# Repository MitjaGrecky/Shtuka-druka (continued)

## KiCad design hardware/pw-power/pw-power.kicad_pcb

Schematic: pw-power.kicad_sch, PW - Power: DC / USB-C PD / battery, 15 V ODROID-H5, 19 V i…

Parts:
C1: 10u; C_0805_2012Metric
C2: 4.7u; C_0603_1608Metric
C3: 10u 50V; C_1206_3216Metric
C4, C93, C105, C153: 10n 50V; C_0603_1608Metric
C5, C6: 47u 35V; CP_Elec_6.3x5.9; LCSC C178565
C7, C8: 330p; C_0402_1005Metric
C9, C10, C114, C115, C116, C121, C122, C123, C143, C144, C145, C150, C151, C152: 22u 25V; C_1210_3225Metric
C11, C125, C126, C129: 10u 25V; C_1210_3225Metric
C12: 47u 35V; CP_Elec_8x10.5
C13, C14, C15, C27, C36, C48, C110, C117, C139, C146: 100n 25V; C_0603_1608Metric
C16, C17, C37, C38: 47n 25V; C_0603_1608Metric
C18, C39: 4.7u 10V; C_0603_1608Metric
C19, C23, C40, C44, C57, C73, C74: 100n 50V; C_0603_1608Metric
C20, C21, C24, C25, C26, C41, C42, C45, C46, C47: 10u 35V; C_1206_3216Metric
C22, C43: 2.2u 35V; C_0805_2012Metric
C28, C29, C30, C31, C32, C33, C34, C49, C50, C51, C52, C53, C54, C55: 10u 25V; C_1206_3216Metric
C35, C56: 1n 50V; C_0402_1005Metric
C58, C61: 100n; C_0603_1608Metric
C59, C60, C111, C118, C124, C127, C140, C147: 1u; C_0603_1608Metric
C62: 100u 35V; CP_Elec_10x10.5
C63, C64: 150u 35V; CP_Elec_8x10.5; MPN EEH-ZA1V151P
C65, C66, C112, C119, C120, C141, C148: 10u 50V; C_1210_3225Metric
C67: 1u 50V; C_0805_2012Metric
C68: 220p; C_0402_1005Metric
C69, C86, C98: 100n; C_0402_1005Metric
C70: 33n; C_0402_1005Metric
C71: 560p; C_0402_1005Metric
C72, C131: 1u 25V; C_0603_1608Metric
C75: 47p; C_0402_1005Metric
C76, C77, C78, C79: 4.7u 50V; C_1210_3225Metric
C80, C81, C82, C83: 10u 35V; C_1210_3225Metric
C84, C85: 100u 35V; CP_Elec_8x10.5
C87, C99: 4.7u; C_0805_2012Metric
C88, C100: 47n; C_0603_1608Metric
C89, C90, C91, C92, C101, C102, C103, C104: 2.2u 50V; C_1206_3216Metric
C94, C95, C96, C97, C106, C107, C108, C109: 47u 10V; C_1210_3225Metric
C113, C142, C149: 220n 50V; C_0603_1608Metric
C128: 10n; C_0402_1005Metric
C130: 47u 25V; C_1210_3225Metric
C132: 47n; C_0402_1005Metric
C133: 22n; C_0402_1005Metric
C134: 470p; C_0402_1005Metric
C135, C136, C138: 4.7u 100V; C_1210_3225Metric
C137: 1u 100V; C_1206_3216Metric
C154, C155, C156, C157: 470u 25V; CP_Elec_10x10.5; MPN EEE-FK1E471P
D1, D2: SMBJ20CA; D_SMB; LCSC C151258
D3, D5: SMBJ13CA; D_SMB; LCSC C224008
D4, D6, D8: green; LED_0603_1608Metric; LCSC C84267
D7: SS1H10; D_SMA; LCSC C3151624
D9: BZT52C3V3; D_SOD-123; LCSC C173413
D10, D11: SS34; D_SMA; LCSC C8678
F1, F2: 10A; Fuse_2920_7451Metric
H1, H2, H3, H4: M3; MountingHole_3.2mm_M3_ISO7380
J1: USB-C Power in; Molex_Micro-Fit_3.0_43045-0612_2x03_P3.00mm_Vertical; LCSC C234188
J2: Battery 1; Molex_Micro-Fit_3.0_43045-0612_2x03_P3.00mm_Vertical; LCSC C234188
J3: Battery 2; Molex_Micro-Fit_3.0_43045-0612_2x03_P3.00mm_Vertical; LCSC C234188
J4: On/Off switch; Molex_Micro-Fit_3.0_43045-0412_2x02_P3.00mm_Vertical; LCSC C277721
J5: Power telemetry to P2; JST_PH_B8B-PH-K_1x08_P2.00mm_Vertical; LCSC C157974
J6: 15 V to H5; Molex_Micro-Fit_3.0_43045-0412_2x02_P3.00mm_Vertical; LCSC C277721
J7: +5V panel; Molex_Micro-Fit_3.0_43045-0612_2x03_P3.00mm_Vertical; LCSC C234188
J8: to R2; JST_PH_B5B-PH-K_1x05_P2.00mm_Vertical; LCSC C157993
J9: to A1/R1; Molex_Micro-Fit_3.0_43045-1012_2x05_P3.00mm_Vertical; LCSC C277725
J10: to F1; JST_PH_B4B-PH-K_1x04_P2.00mm_Vertical; LCSC C131334
J11: +5V screen; JST_PH_B2B-PH-K_1x02_P2.00mm_Vertical; LCSC C131337
J12: Fan 12 V PWM; PinHeader_1x04_P2.54mm_Vertical; LCSC C2691448
L1, L2: 1uH; L_Bourns_SRP7028A_7.3x6.6mm; LCSC C87572
L3: 4.7uH; L_Bourns_SRP1245A
L4, L5: 4.7uH; L_Bourns_SRP1038C_10.0x10.0mm; MPN SRP1038CC-4R7M
L6, L7, L9, L10: 10uH; L_Bourns_SRN6045TA
L8: 22uH; L_Bourns_SRN6045TA
Q1, Q2, Q3, Q6, Q9, Q10, Q11, Q12: CSD18532Q5B; TDSON-8-1; LCSC C882766
Q4, Q5, Q7, Q8: 2N7002; SOT-23; LCSC C8545
Q13: IRLML0100; SOT-23; LCSC C53658
R1, R3: 42.2k; R_0402_1005Metric
R2, R4, R5, R6, R7, R8, R18, R19, R29, R30, R34, R35, R42, R45, R71, R73, R77, R84: 10k; R_0402_1005Metric
R9, R20: 0 wire 1mm2; SolderWire-1sqmm_1x02_P5.4mm_D1.4mm_OD2.7mm
R10, R21: 2; R_0805_2012Metric
R11, R22, R75, R83, R85: 100; R_0402_1005Metric
R12, R23: 10.5k; R_0402_1005Metric
R13, R24: 47k; R_0402_1005Metric
R14, R16, R25, R27, R36, R53, R60, R62, R64, R68, R79, R81: 100k; R_0402_1005Metric
R15, R26: 9.31k; R_0402_1005Metric
R17, R28, R78: 2.2k; R_0402_1005Metric
R31: 5m; R_2512_6332Metric
R32, R33, R37: 10; R_0603_1608Metric
R38: 249k; R_0402_1005Metric
R39: 32.4k; R_0402_1005Metric
R40: 93.1k; R_0402_1005Metric
R41: 27.4k; R_0402_1005Metric
R43: 453k; R_0402_1005Metric
R44: 20k; R_0402_1005Metric
R46: 8m; R_2512_6332Metric
R47: 100; R_0603_1608Metric
R48, R55: 392k; R_0402_1005Metric
R49, R56, R70: 49.9k; R_0402_1005Metric
R50, R57: 54.9k; R_0402_1005Metric
R51, R58: 41.2k; R_0402_1005Metric
R52, R59: 24.9k; R_0402_1005Metric
R54, R61: 6.8m; R_2512_6332Metric
R63, R65: 7.68k; R_0402_1005Metric
R66: 102k; R_0402_1005Metric
R67: 11k; R_0402_1005Metric
R69: 27k; R_0402_1005Metric
R72: 475k; R_0402_1005Metric
R74: 0.1; R_0603_1608Metric
R76: 383k; R_0402_1005Metric
R80: 7.15k; R_0402_1005Metric
R82: 9.09k; R_0402_1005Metric
R86: 357k; R_0402_1005Metric
R87: 118k; R_0402_1005Metric
R88: 26.7k; R_0402_1005Metric
R89: 3.32k; R_0402_1005Metric
R90: 220k; R_0402_1005Metric
R91, R93: 0; R_1206_3216Metric
R92, R94: 10; R_2512_6332Metric
R95, R96, R97, R98, R99, R100: 1k; R_2512_6332Metric
R101, R102: 820; R_2512_6332Metric
TP1: VBUS; TestPoint_Pad_D2.0mm
TP2: BUS; TestPoint_Pad_D2.0mm
TP3: P14; TestPoint_Pad_D2.0mm
TP4: N14; TestPoint_Pad_D2.0mm
TP5: +5V; TestPoint_Pad_D2.0mm
TP6: +5V_PANEL; TestPoint_Pad_D2.0mm
TP7: +3V3; TestPoint_Pad_D2.0mm
TP8, TP9, TP10: GND; TestPoint_Pad_D2.0mm
U1: TPS25730D; Texas_REF0038A_WQFN-38-2EP_6x4mm_P0.4; LCSC C22438973
U2, U3, U4, U6: LM74700-Q1; SOT-23-6; LCSC C2941042
U5, U7: BQ25798; Texas_RQM0029A_VQFN-29_4x4mm_P0.4mm; LCSC C2876593
U8: INA226; MSOP-10_3x3mm_P0.5mm; LCSC C49851
U9: AP2112K-3.3; SOT-23-5; LCSC C51118
U10: TCA9546APW; TSSOP-16_4.4x5mm_P0.65mm; LCSC C201653
U11: LM5176; HTSSOP-28-1EP_4.4x9.7mm_P0.65mm_EP3.4x9.5mm_ThermalVias; LCSC C442493
U12, U13: LM70660; VQFN-29_RRX0029B_6x6_P0.5mm; LCSC C42328952
U14, U15, U20, U21: LMR33640; Texas_HSOP-8-1EP_3.9x4.9mm_P1.27mm_ThermalVias; LCSC C2836966
U16: TPS7A4701; Texas_RGW0020A_VQFN-20-1EP_5x5mm_P0.65mm_EP3.15x3.15mm_Ther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; LCSC C90084
U17: TPS7A3301; Texas_RGW0020A_VQFN-20-1EP_5x5mm_P0.65mm_EP3.15x3.15mm_Ther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; LCSC C90082
U18: LM5156H; Texas_HTSSOP-14-1EP_4.4x5mm_P0.65mm_EP3.4x5mm_Mask3.155x3.2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; LCSC C2867852
U19: TPS7A4101; Texas_DGN0008B_VSSOP-8-1EP_3x3mm_P0.65mm_EP2x3mm_Mask1.88x1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; LCSC C111739
U22: TPS26631RGER; QFN-24-1EP_4x4mm_P0.5mm_EP2.65x2.65mm; LCSC C1850273

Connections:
+3V3: C58.1, C60.1, C61.1, Q5.1 (G), Q8.1 (G), R18.2, R19.2, R29.2, R30.2, R34.2, R35.2, R84.2, TP7.1, U8.6 (VS), U9.5 (VOUT), U10.16 (VCC)
+5V: C59.1, C106.1, C107.1, C108.1, C109.1, J8.5, J9.5, J9.9, J10.4, J11.1, R61.2, R78.1, TP5.1, U9.1 (VIN), U9.3 (EN), U13.6 (BIAS), U13.12 (VOUT)
/+5V_PANEL: C94.1, C95.1, C96.1, C97.1, J7.1, J7.2, J7.3, R54.2, TP6.1, U12.6 (BIAS), U12.12 (VOUT)
/+12V: C126.1, J8.1, J9.1, J10.1, U16.1 (OUT), U16.3 (SENSE/FB), U16.20 (OUT)
/+48V: C138.1, J9.7, R76.1, U19.1 (OUT)
/-12V: C128.1, C130.2, J8.3, J9.3, J10.3, R66.1, U17.1 (OUT), U17.20 (OUT)
/B19_BOOT1: C73.1, U11.26 (BOOT1)
/B19_BOOT2: C74.1, U11.20 (BOOT2)
/B19_CMP_RC: C70.1, R42.2
/B19_COMP: C71.1, R42.1, U11.9 (COMP)
/B19_CS: C75.1, R47.2, U11.16 (CS)
/B19_CSN: Q10.1 (S), Q10.2 (S), Q10.3 (S), Q12.1 (S), Q12.2 (S), Q12.3 (S), R46.1, R47.1
/B19_FB: R43.2, R44.1, U11.11 (FB)
/B19_HDRV1: Q9.4 (G), U11.27 (HDRV1)
/B19_HDRV2: Q11.4 (G), U11.19 (HDRV2)
/B19_LDRV1: Q10.4 (G), U11.25 (LDRV1)
/B19_LDRV2: Q12.4 (G), U11.21 (LDRV2)
/B19_MODE: R40.1, U11.4 (MODE)
/B19_PG: R45.1, U11.17 (PGOOD)
/B19_RT: R41.1, U11.6 (RT/SYNC)
/B19_SLOPE: C68.1, U11.7 (SLOPE)
/B19_SS: C69.1, U11.8 (SS)
/B19_SW1: C73.2, L3.1, Q9.1 (S), Q9.2 (S), Q9.3 (S), Q10.5 (D), U11.28 (SW1)
/B19_SW2: C74.2, L3.2, Q11.1 (S), Q11.2 (S), Q11.3 (S), Q12.5 (D), U11.18 (SW2)
/B19_UVLO: R38.2, R39.1, U11.1 (EN/UVLO)
/B19_VCC: C72.1, R45.2, U11.23 (VCC)
/B19_VIN: C67.1, R37.2, U11.2 (VIN), U11.3 (VISNS)
/BAT1_F: C15.2, C33.1, C34.1, D3.1 (A1), F1.2, Q3.1 (S), Q3.2 (S), Q3.3 (S), R11.1, U4.3 (EN), U4.6 (ANODE), U5.22 (BAT), U5.23 (BAT)
/BAT1_J: F1.1, R9.2
/BAT1_RAW: J2.1, J2.2, R9.1
/BAT2_F: C36.2, C54.1, C55.1, D5.1 (A1), F2.2, Q6.1 (S), Q6.2 (S), Q6.3 (S), R22.1, U6.3 (EN), U6.6 (ANODE), U7.22 (BAT), U7.23 (BAT)
/BAT2_J: F2.1, R20.2
/BAT2_RAW: J3.1, J3.2, R20.1
/BUS: C62.1, C63.1, C64.1, C65.1, C66.1, C76.1, C77.1, C78.1, C79.1, C89.1, C90.1, C91.1, C92.1, C93.1, C101.1, C102.1, C103.1, C104.1, C105.1, Q9.5 (D), R31.2, R33.1, R37.1, R38.1, R48.1, R55.1, TP2.1, U8.8 (Vbus), U12.1 (VIN), U12.2 (VIN), U12.3 (VIN), U12.27 (VIN), U12.28 (VIN), U12.29 (VIN), U13.1 (VIN), U13.2 (VIN), U13.3 (VIN), U13.27 (VIN), U13.28 (VIN), U13.29 (VIN)
/BUS_IN: J4.1, J4.2, Q2.5 (D), Q3.5 (D), Q6.5 (D), U3.4 (CATHODE), U4.4 (CATHODE), U6.4 (CATHODE)
/BUS_SW: J4.3, J4.4, R31.1, R32.1
/CH1_BATP: R11.2, U5.18 (BATP)
/CH1_BTST1: C16.1, U5.4 (BTST1)
/CH1_BTST2: C17.1, U5.19 (BTST2)
/CH1_CE: Q4.3 (D), R16.2, U5.13 (~CE)
/CH1_CEM: Q4.2 (S), Q5.3 (D)
/CH1_ILIM: R13.2, R14.1, U5.17 (ILIM_HIZ)
/CH1_LEDA: D4.2 (A), R17.2
/CH1_PMID: C23.1, C24.1, C25.1, C26.1, U5.29 (PMID)
/CH1_PROG: R12.1, U5.20 (PROG)
/CH1_REGN: C18.1, R13.1, R15.1, R16.1, R17.1, U5.5 (REGN)
/CH1_SCL: R18.1, U5.14 (SCL), U10.5 (SC0)
/CH1_SDA: R19.1, U5.15 (SDA), U10.4 (SD0)
/CH1_SDRV: C35.1, U5.24 (SDRV)
/CH1_SNUB: C22.1, R10.2
/CH1_STAT: D4.1 (K), U5.1 (STAT)
/CH1_SW1: C16.2, L1.1, U5.28 (SW1)
/CH1_SW2: C17.2, L1.2, U5.26 (SW2)
/CH1_SYS: C27.1, C28.1, C29.1, C30.1, C31.1, C32.1, U5.25 (SYS)
/CH1_TS: J2.5, R15.2, U5.16 (TS)
/CH2_BATP: R22.2, U7.18 (BATP)
/CH2_BTST1: C37.1, U7.4 (BTST1)
/CH2_BTST2: C38.1, U7.19 (BTST2)
/CH2_CE: Q7.3 (D), R27.2, U7.13 (~CE)
/CH2_CEM: Q7.2 (S), Q8.3 (D)
/CH2_ILIM: R24.2, R25.1, U7.17 (ILIM_HIZ)
/CH2_LEDA: D6.2 (A), R28.2
/CH2_PMID: C44.1, C45.1, C46.1, C47.1, U7.29 (PMID)
/CH2_PROG: R23.1, U7.20 (PROG)
/CH2_REGN: C39.1, R24.1, R26.1, R27.1, R28.1, U7.5 (REGN)
/CH2_SCL: R29.1, U7.14 (SCL), U10.7 (SC1)
/CH2_SDA: R30.1, U7.15 (SDA), U10.6 (SD1)
/CH2_SDRV: C56.1, U7.24 (SDRV)
/CH2_SNUB: C43.1, R21.2
/CH2_STAT: D6.1 (K), U7.1 (STAT)
/CH2_SW1: C37.2, L2.1, U7.28 (SW1)
/CH2_SW2: C38.2, L2.2, U7.26 (SW2)
/CH2_SYS: C48.1, C49.1, C50.1, C51.1, C52.1, C53.1, U7.25 (SYS)
/CH2_TS: J3.5, R26.2, U7.16 (TS)
/CHG_EN: J5.8, Q4.1 (G), Q7.1 (G), R36.1
/CHG_INT: J5.4, R35.1, U5.21 (~INT), U7.21 (~INT)
/EXT: C14.2, C19.1, C20.1, C21.1, C40.1, C41.1, C42.1, D2.1 (A1), Q1.5 (D), Q2.1 (S), Q2.2 (S), Q2.3 (S), R10.1, R21.1, U2.4 (CATHODE), U3.3 (EN), U3.6 (ANODE), U5.2 (VBUS), U5.3 (VBUS), U5.8 (VAC2), U5.9 (VAC1), U7.2 (VBUS), U7.3 (VBUS), U7.8 (VAC2), U7.9 (VAC1)
/FAN_PWM: J12.4, R83.2
/FAN_PWM_IN: J5.5, R83.1
/FAN_TACH: J12.3, R84.1, R85.1
/FAN_TACH_OUT: J5.6, R85.2
/HV_COMP: C134.1, R71.1, U18.8 (COMP)
/HV_CRC: C133.1, R71.2
/HV_CS: R75.2, U18.7 (CS)
/HV_CSN: Q13.2 (S), R74.1, R75.1
/HV_FB: R72.2, R73.1, U18.10 (FB)
/HV_GATE: Q13.1 (G), U18.4 (GATE)
/HV_RAW: C135.1, C136.1, C137.1, D7.1 (K), R72.1, U19.5 (EN), U19.8 (IN)
/HV_RT: R70.1, U18.12 (RT)
/HV_SS: C132.1, U18.11 (SS)
/HV_SW: D7.2 (A), L8.2, Q13.3 (D)
/HV_UVLO: R68.2, R69.1, U18.14 (EN/UVLO/SYNC)
/HV_VCC: C131.1, U18.3 (VCC), U18.9 (DITHOFF)
/IBAT1_GATE: Q3.4 (G), U4.5 (GATE)
/IBAT1_VCAP: C15.1, U4.1 (VCAP)
/IBAT2_GATE: Q6.4 (G), U6.5 (GATE)
/IBAT2_VCAP: C36.1, U6.1 (VCAP)
/IEXT_GATE: Q2.4 (G), U3.5 (GATE)
/IEXT_VCAP: C14.1, U3.1 (VCAP)
/IPD_GATE: Q1.4 (G), U2.5 (GATE)
/IPD_VCAP: C13.1, U2.1 (VCAP)
/LED_K: D8.2 (A), R78.2
/MUX_RST: R34.1, U10.3 (~RESET)
/N12_FB: C128.2, R66.2, R67.1, U17.3 (FB)
/N12_NR: C127.1, U17.14 (NR/SS)
/N14: C118.2, C119.2, C121.2, C122.2, C123.2, C129.2, D11.2 (A), R65.2, R94.1, R97.1, R98.1, TP4.1, U15.1 (GND), U15.9 (GND), U17.13 (EN), U17.15 (IN), U17.16 (IN)
/N14_BOOT: C117.1, U15.7 (BOOT)
/N14_C: C156.2, C157.2, R93.2
/N14_FB: R64.2, R65.1, U15.5 (FB)
/N14_ST: D11.1 (K), R93.1, R94.2
/N14_SW: C117.2, L7.1, U15.8 (SW)
/N14_VCC: C118.1, U15.6 (VCC)
/P5VPANEL_BOOT: C88.1, U12.4 (CBOOT)
/P5VPANEL_CFG: R51.1, U12.13 (CONFIG)
/P5VPANEL_EN: R48.2, R49.1, U12.9 (EN/UVLO)
/P5VPANEL_FB: R52.1, U12.16 (FB)
/P5VPANEL_LS: L4.2, R54.1, U12.11 (ISNS+)
/P5VPANEL_RT: R50.1, U12.14 (RT)
/P5VPANEL_SW: C88.2, L4.1, U12.5 (SW4), U12.20 (SW), U12.21 (SW), U12.22 (SW)
/P5VPANEL_VCC: C87.1, U12.19 (VCC)
/P5VPANEL_VDDA: C86.1, R52.2, R53.2, U12.18 (VDDA)
/P5VPANEL_XC: R53.1, U12.15 (EXTCOMP)
/P5V_BOOT: C100.1, U13.4 (CBOOT)
/P5V_CFG: R58.1, U13.13 (CONFIG)
/P5V_EN: R55.2, R56.1, U13.9 (EN/UVLO)
/P5V_FB: R59.1, U13.16 (FB)
/P5V_LS: L5.2, R61.1, U13.11 (ISNS+)
/P5V_RT: R57.1, U13.14 (RT)
/P5V_SW: C100.2, L5.1, U13.5 (SW4), U13.20 (SW), U13.21 (SW), U13.22 (SW)
/P5V_VCC: C99.1, U13.19 (VCC)
/P5V_VDDA: C98.1, R59.2, R60.2, U13.18 (VDDA)
/P5V_XC: R60.1, U13.15 (EXTCOMP)
/P12_NR: C124.1, U16.14 (NR)
/P14: C114.1, C115.1, C116.1, C125.1, D10.1 (K), L6.2, R62.1, R92.1, R95.1, R96.1, TP3.1, U16.13 (EN), U16.15 (IN), U16.16 (IN)
/P14_BOOT: C110.1, U14.7 (BOOT)
/P14_C: C154.1, C155.1, R91.2
/P14_FB: R62.2, R63.1, U14.5 (FB)
/P14_ST: D10.2 (A), R91.1, R92.2
/P14_SW: C110.2, L6.1, U14.8 (SW)
/P14_VCC: C111.1, U14.6 (VCC)
/P48_FB: R76.2, R77.1, U19.2 (FB)
/PDF_DVDT: C153.1, U22.9 (dVdT)
/PDF_ILIM: R89.1, U22.10 (ILIM)
/PDF_OV: R87.2, R88.1, U22.7 (OVP)
/PDF_SHDN: D9.2 (K), R90.2, U22.12 (SHDN)
/PDF_UV: R86.2, R87.1, U22.6 (UVLO)
/PD_ADCIN1: R1.2, R2.1, U1.2 (ADCIN1)
/PD_ADCIN34: R3.2, R4.1, U1.5 (ADCIN3), U1.7 (ADCIN4)
/PD_CC1: C7.1, J1.5, U1.28 (CC1)
/PD_CC2: C8.1, J1.6, U1.29 (CC2)
/PD_DRAIN: U1.15 (DRAIN), U1.30 (DRAIN), U1.40 (DRAIN)
/PD_FAULT: R5.1, U1.18 (~FAULT_IN)
/PD_LDO1V5: C2.1, U1.4 (LDO_1V5)
/PD_LDO3V3: C1.1, R1.1, R3.1, R5.2, U1.1 (LDO_3V3), U1.3 (ADCIN2)
/PD_OUT: C9.1, C10.1, C11.1, C12.1, C13.2, Q1.1 (S), Q1.2 (S), Q1.3 (S), U1.20 (PPHV), U2.3 (EN), U2.6 (ANODE)
/PD_RSV26: R6.1, U1.26 (RESERVED)
/PD_RSV27: R7.1, U1.27 (RESERVED)
/PD_RSV36: R8.1, U1.36 (RESERVED)
/PD_VBUS: C5.1, C6.1, D1.1 (A1), J1.1, J1.2, R86.1, R90.1, TP1.1, U22.1 (IN), U22.2 (IN), U22.5 (IN_SYS)
/PD_VBUSF: C3.1, C4.1, U1.23 (VBUS_IN), U1.32 (VBUS), U22.17 (OUT), U22.18 (OUT)
/PM_ALERT: J5.3, U8.3 (~Alert)
/PM_INN: C57.2, R33.2, U8.9 (Vin-)
/PM_INP: C57.1, R32.2, U8.10 (Vin+)
/PM_SCL: J5.2, U8.5 (SCL), U10.14 (SCL)
/PM_SDA: J5.1, U8.4 (SDA), U10.15 (SDA)
/V12F: C150.1, C151.1, C152.1, J12.2, L10.2, R81.1, R101.1, R102.1
/V12F_BOOT: C146.1, U21.7 (BOOT)
/V12F_FB: R81.2, R82.1, U21.5 (FB)
/V12F_SW: C146.2, L10.1, U21.8 (SW)
/V12F_VCC: C147.1, U21.6 (VCC)
/V15: C143.1, C144.1, C145.1, J6.1, J6.2, L9.2, R79.1, R99.1, R100.1
/V15_BOOT: C139.1, U20.7 (BOOT)
/V15_FB: R79.2, R80.1, U20.5 (FB)
/V15_SW: C139.2, L9.1, U20.8 (SW)
/V15_VCC: C140.1, U20.6 (VCC)
/V19: C80.1, C81.1, C82.1, C83.1, C84.1, C85.1, C112.1, C113.1, C119.1, C120.1, C141.1, C142.1, C148.1, C149.1, L8.1, Q11.5 (D), R43.1, R68.1, U11.12 (VOSNS), U11.13 (ISNS(-)), U11.14 (ISNS(+)), U11.24 (BIAS), U14.2 (VIN), U14.3 (EN), U15.2 (VIN), U15.3 (EN), U18.1 (BIAS), U20.2 (VIN), U20.3 (EN), U21.2 (VIN), U21.3 (EN)
GND: C1.2, C2.2, C3.2, C4.2, C5.2, C6.2, C7.2, C8.2, C9.2, C10.2, C11.2, C12.2, C18.2, C19.2, C20.2, C21.2, C22.2, C23.2, C24.2, C25.2, C26.2, C27.2, C28.2, C29.2, C30.2, C31.2, C32.2, C33.2, C34.2, C35.2, C39.2, C40.2, C41.2, C42.2, C43.2, C44.2, C45.2, C46.2, C47.2, C48.2, C49.2, C50.2, C51.2, C52.2, C53.2, C54.2, C55.2, C56.2, C58.2, C59.2, C60.2, C61.2, C62.2, C63.2, C64.2, C65.2, C66.2, C67.2, C68.2, C69.2, C70.2, C71.2, C72.2, C75.2, C76.2, C77.2, C78.2, C79.2, C80.2, C81.2, C82.2, C83.2, C84.2, C85.2, C86.2, C87.2, C89.2, C90.2, C91.2, C92.2, C93.2, C94.2, C95.2, C96.2, C97.2, C98.2, C99.2, C101.2, C102.2, C103.2, C104.2, C105.2, C106.2, C107.2, C108.2, C109.2, C111.2, C112.2, C113.2, C114.2, C115.2, C116.2, C120.2, C121.1, C122.1, C123.1, C124.2, C125.2, C126.2, C127.2, C129.1, C130.1, C131.2, C132.2, C133.2, C134.2, C135.2, C136.2, C137.2, C138.2, C140.2, C141.2, C142.2, C143.2, C144.2, C145.2, C147.2, C148.2, C149.2, C150.2, C151.2, C152.2, C153.2, C154.2, C155.2, C156.1, C157.1, D1.2 (A2), D2.2 (A2), D3.2 (A2), D5.2 (A2), D8.1 (K), D9.1 (A), J1.3, J1.4, J2.3, J2.4, J2.6, J3.3, J3.4, J3.6, J5.7, J6.3, J6.4, J7.4, J7.5, J7.6, J8.2, J8.4, J9.2, J9.4, J9.6, J9.8, J9.10, J10.2, J11.2, J12.1, L7.2, Q5.2 (S), Q8.2 (S), R2.2, R4.2, R6.2, R7.2, R8.2, R12.2, R14.2, R23.2, R25.2, R36.2, R39.2, R40.2, R41.2, R44.2, R46.2, R49.2, R50.2, R51.2, R56.2, R57.2, R58.2, R63.2, R64.1, R67.2, R69.2, R70.2, R73.2, R74.2, R77.2, R80.2, R82.2, R88.2, R89.2, R95.2, R96.2, R97.2, R98.2, R99.2, R100.2, R101.2, R102.2, TP8.1, TP9.1, TP10.1, U1.8 (I2Ct_SDA), U1.9 (I2Ct_SCL), U1.11 (GND), U1.12 (GND), U1.14 (GND), U1.16 (GND), U1.17 (GND), U1.31 (GND), U1.34 (GND), U1.38 (VIN_3V3), U1.39 (GND), U2.2 (GND), U3.2 (GND), U4.2 (GND), U5.10 (ACDRV2), U5.11 (ACDRV1), U5.27 (GND), U6.2 (GND), U7.10 (ACDRV2), U7.11 (ACDRV1), U7.27 (GND), U8.1 (A1), U8.2 (A0), U8.7 (GND), U9.2 (GND), U10.1 (A0), U10.2 (A1), U10.8 (GND), U10.13 (A2), U11.5 (DITH), U11.10 (AGND), U11.15 (CSG), U11.22 (PGND), U11.29 (PowerPAD), U12.8 (PFM/SYNCIN), U12.17 (AGND), U12.23 (PGND), U12.24 (PGND), U12.25 (PGND), U12.26 (PGND), U12.30 (EP), U13.8 (PFM/SYNCIN), U13.17 (AGND), U13.23 (PGND), U13.24 (PGND), U13.25 (PGND), U13.26 (PGND), U13.30 (EP), U14.1 (GND), U14.9 (GND), U16.4 (6.4V), U16.6 (3.2V), U16.7 (GND), U16.9 (0.8V), U16.11 (0.2V), U16.21 (EP), U17.7 (GND), U17.21 (EP), U18.5 (PGND), U18.6 (AGND), U18.15 (AGND), U19.4 (GND), U19.9 (GND), U20.1 (GND), U20.9 (GND), U21.1 (GND), U21.9 (GND), U22.8 (GND), U22.11 (MODE), U22.15 (PGTH), U22.25 (EP)

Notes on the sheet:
Input USB-C PD 15-20 V (TPS25730D, also a MacBook charger; the DC input is removed, R205) -> EXT; EXT and two 3S packs (each with its own BQ25798 charger from EXT) -> ideal diodes (LM74700) -> rear On/Off switch -> BUS 9-24 V (packs 9-12.6 V) -> 19 V internal rail (LM5176) -> 15 V H5 (LMR33640), +5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
Values after the TI datasheet examples, scaled; every 'check' note is verified before the board
Rev 0.1: schematic only (R145: USB-C Power is separate from the isolated USB-C PC port)

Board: 4 copper layers, 343 parts (243 on the bottom side), 177 nets, no tracks yet.

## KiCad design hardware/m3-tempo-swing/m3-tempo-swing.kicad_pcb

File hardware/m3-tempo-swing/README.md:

# M3 - Tempo + Swing (encoder module)

Two smooth encoders with push (Tempo, Swing) and a 12-LED RGB ring around each. Spec: `hardware/for-routing/SPEC_boards.md`, section M3.
Status: rev 0.2 (rings r 15 from the layout, V2) - schematic and placed board with mounts, not routed (`UNROUTED`). Package for EasyEDA Pro: `hardware/for-routing/M3/`.

| | |
|---|---|
| Board | 92 x 34 mm, 2 layers; panel x 10-102, y 263-297 (the M1 strip, left column) |
| Top side | 2 x Alps EC11E smooth with switch (shafts at panel x 32 and 80, y 277; knob 22 mm), 24 x XL-1615RGBC-RF (C965840) on rings r 15 mm (layout ring 30; V2, user 13.11: the layout wins over the spec formula), 270 degrees |
| Bottom side | LP5864 LED driver (C5220564), 74HC165 (C80696), 2 x 4x10k packs (C25725), passives, J1 |
| Bus | J1 2 x 7, 1.27 mm (R123) at the front edge, to P1 (I2C channel 1 of P1's TCA9546A, P99) |
| I2C | LP5864 0x40 (ADDR1 ADDR0 = 0 0); SDA/SCL pull-ups R1, R2 not fitted (on the host); ~INT not used |
| Shift chain | host reads D7..D0: Tempo A, Tempo B, Tempo push, Swing A, Swing B, Swing push, 1, 1; DS <- SR_IN (R3 10k pull-up) |
| LEDs | left ring (Tempo) CS9-17, right ring (Swing) CS0-8; runs of 4 dots share a CS triple, SW0-3 serpentine (as M1 rev 0.5) |
| Touch | none (P102, proposal): encoder frames MP on GND; `design.TOUCH` marks the switch point |
| Holes | M2 in the corners and one between the knobs at the rear edge |

Checks (12.11.2026, KiCad 10.0.8): ERC 0 errors (4 warnings: ~INT on one pin, two library symbol versions);
`check_netlist.py` 202 pins, 0 mismatches; DRC 0 errors, schematic parity 0, 163 unrouted (by design);
EasyEDA Pro 3.2.209 import (project M3_v4, rev 0.2): PCB 38/38 and schematic 38/38 nets, 46/46 parts.

## Files and generators

Shared blocks: `hardware/common/gen/kit.py` (bus, LP5864, 74HC165, encoder, rings, holes), `boardkit.py`, `check_netlist.py`.
The schematic writer is M1's (`m1-screen-knobs/gen/make_sch.py`), loaded through `common/gen/m1compat.py` (Python 3.11).

```
python gen/design.py            # parts, nets, placement summary
python gen/make_sch.py          # schematic (KiCad 7 format)
python gen/check_netlist.py     # schematic netlist == design.py, pin by pin
python gen/make_pcb.py          # placed board, nets, mounts; no routing
python ../../tools/pack_easyeda.py M3 .     # package for EasyEDA (PC, KiCad 9/10)
```

On a PC with KiCad 10 set `KICAD_SYMBOL_DIR=<repo>/hardware/common/sym7` (built by `python ../common/gen/sym7.py`)
and `KICAD_FOOTPRINT_DIR=<KiCad>/share/kicad/footprints`; run with KiCad's Python. The board written by KiCad 10's pcbnew
is in the KiCad 10 format; the cloud (KiCad 7) regenerates it with `make_pcb.py`.

License: CERN-OHL-S-2.0 (hardware), AGPL-3.0-or-later (scripts).

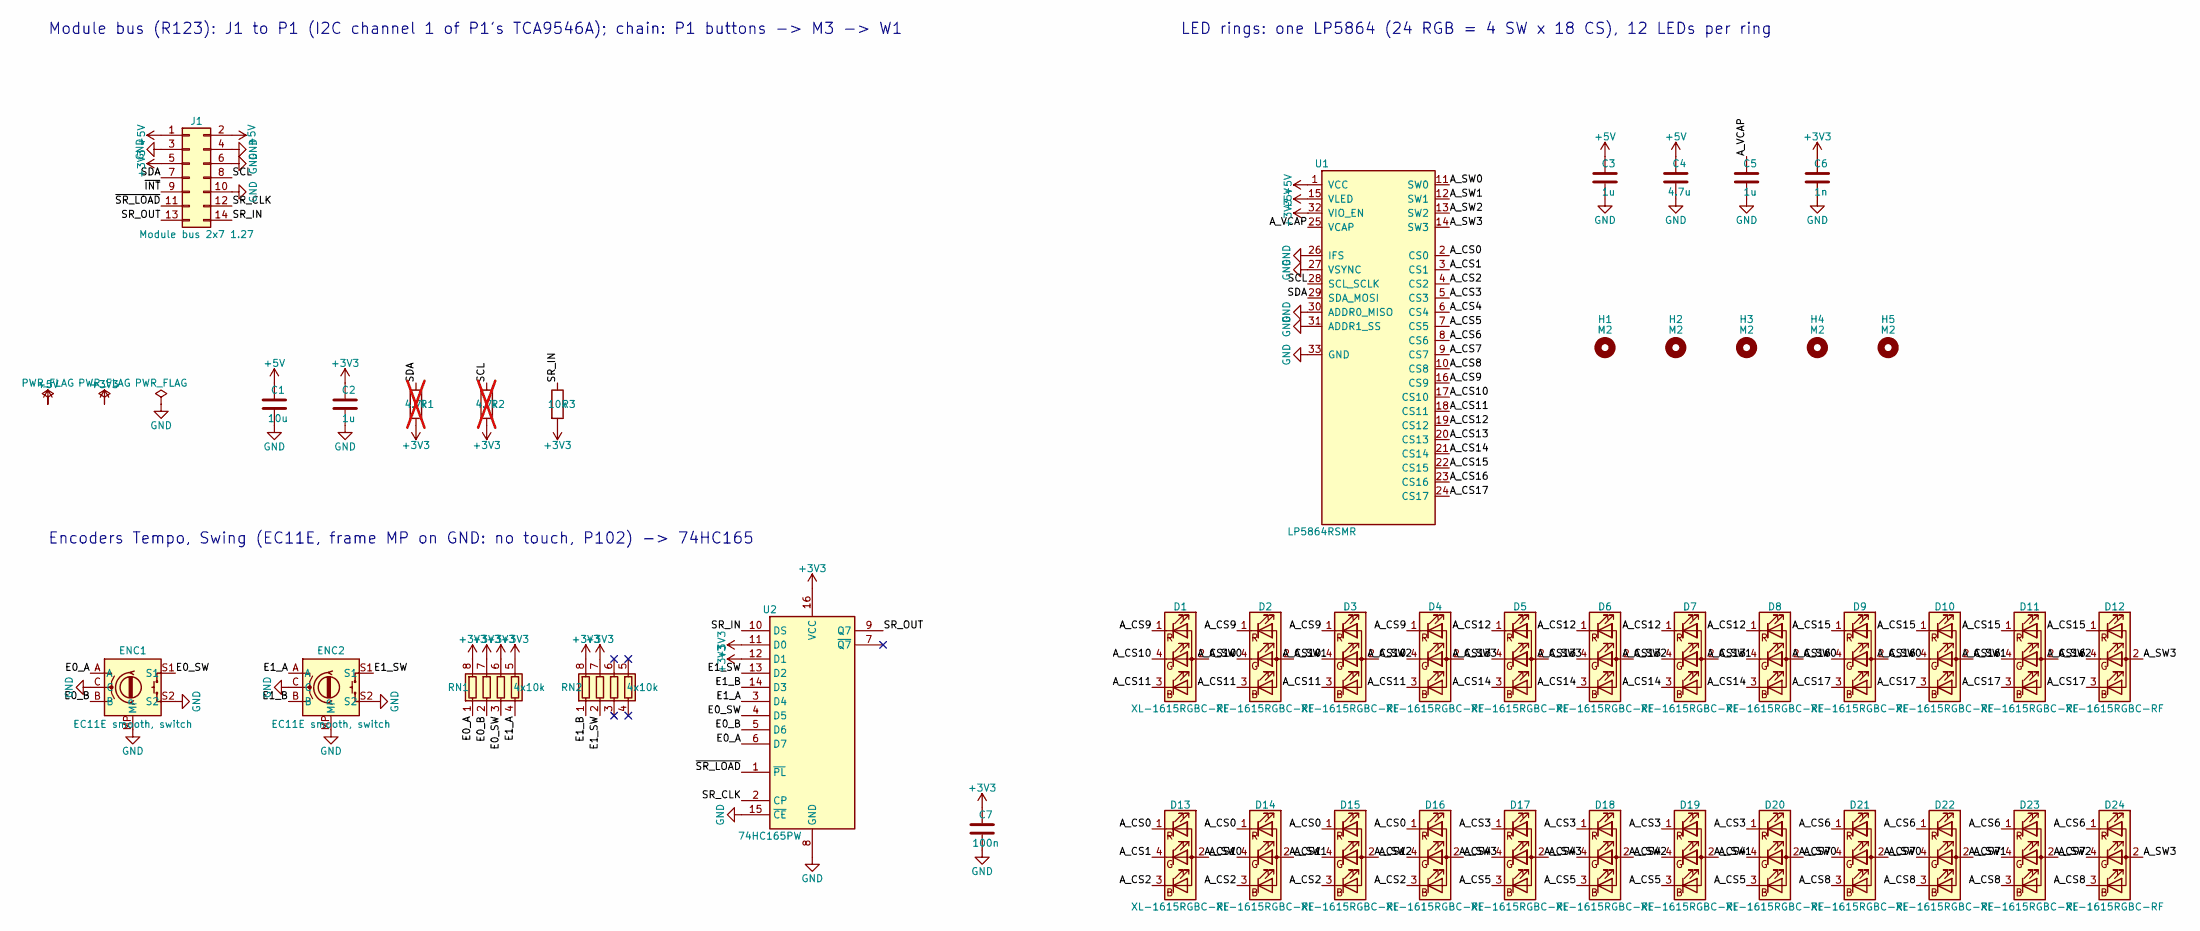
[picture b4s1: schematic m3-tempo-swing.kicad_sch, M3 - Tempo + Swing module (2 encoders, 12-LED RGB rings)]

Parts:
C1: 10u; C_0805_2012Metric; LCSC C15850
C2, C3, C5: 1u; C_0402_1005Metric; LCSC C52923
C4: 4.7u; C_0805_2012Metric; LCSC C1779
C6: 1n; C_0402_1005Metric; LCSC C1523
C7: 100n; C_0402_1005Metric; LCSC C1525
D1, D2, D3, D4, D5, D6, D7, D8, D9, D10, D11, D12, D13, D14, D15, D16, D17, D18, D19, D20, D21, D22, D23, D24: XL-1615RGBC-RF; LED_RGB_XL-1615RGBC_1.6x1.5mm; LCSC C965840
ENC1, ENC2: EC11E smooth, switch; RotaryEncoder_Alps_EC11E-Switch_Vertical_H20mm_Ring; LCSC C361165
H1, H2, H3, H4, H5: M2; MountingHole_2.2mm_M2
J1: Module bus 2x7 1.27; PinHeader_2x07_P1.27mm_Vertical; LCSC C5372811
R1, R2: 4.7k; R_0402_1005Metric; LCSC C25900; not fitted
R3: 10k; R_0402_1005Metric; LCSC C25744
RN1, RN2: 4x10k; R_Array_Convex_4x0402; LCSC C25725
U1: LP5864RSMR; VQFN-32-1EP_4x4mm_P0.4mm_EP2.8x2.8mm; LCSC C5220564
U2: 74HC165PW; TSSOP-16_4.4x5mm_P0.65mm; LCSC C80696

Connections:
+3V3: C2.1, C6.1, C7.1, J1.5, R1.2, R2.2, R3.2, RN1.5 (R4.2), RN1.6 (R3.2), RN1.7 (R2.2), RN1.8 (R1.2), RN2.7 (R2.2), RN2.8 (R1.2), U1.32 (VIO_EN), U2.11 (D0), U2.12 (D1), U2.16 (VCC)
+5V: C1.1, C3.1, C4.1, J1.1, J1.2, U1.1 (VCC), U1.15 (VLED)
/A_CS0: D13.1 (RK), D14.1 (RK), D15.1 (RK), D16.1 (RK), U1.2 (CS0)
/A_CS1: D13.4 (GK), D14.4 (GK), D15.4 (GK), D16.4 (GK), U1.3 (CS1)
/A_CS2: D13.3 (BK), D14.3 (BK), D15.3 (BK), D16.3 (BK), U1.4 (CS2)
/A_CS3: D17.1 (RK), D18.1 (RK), D19.1 (RK), D20.1 (RK), U1.5 (CS3)
/A_CS4: D17.4 (GK), D18.4 (GK), D19.4 (GK), D20.4 (GK), U1.6 (CS4)
/A_CS5: D17.3 (BK), D18.3 (BK), D19.3 (BK), D20.3 (BK), U1.7 (CS5)
/A_CS6: D21.1 (RK), D22.1 (RK), D23.1 (RK), D24.1 (RK), U1.8 (CS6)
/A_CS7: D21.4 (GK), D22.4 (GK), D23.4 (GK), D24.4 (GK), U1.9 (CS7)
/A_CS8: D21.3 (BK), D22.3 (BK), D23.3 (BK), D24.3 (BK), U1.10 (CS8)
/A_CS9: D1.1 (RK), D2.1 (RK), D3.1 (RK), D4.1 (RK), U1.16 (CS9)
/A_CS10: D1.4 (GK), D2.4 (GK), D3.4 (GK), D4.4 (GK), U1.17 (CS10)
/A_CS11: D1.3 (BK), D2.3 (BK), D3.3 (BK), D4.3 (BK), U1.18 (CS11)
/A_CS12: D5.1 (RK), D6.1 (RK), D7.1 (RK), D8.1 (RK), U1.19 (CS12)
/A_CS13: D5.4 (GK), D6.4 (GK), D7.4 (GK), D8.4 (GK), U1.20 (CS13)
/A_CS14: D5.3 (BK), D6.3 (BK), D7.3 (BK), D8.3 (BK), U1.21 (CS14)
/A_CS15: D9.1 (RK), D10.1 (RK), D11.1 (RK), D12.1 (RK), U1.22 (CS15)
/A_CS16: D9.4 (GK), D10.4 (GK), D11.4 (GK), D12.4 (GK), U1.23 (CS16)
/A_CS17: D9.3 (BK), D10.3 (BK), D11.3 (BK), D12.3 (BK), U1.24 (CS17)
/A_SW0: D1.2 (A), D8.2 (A), D9.2 (A), D13.2 (A), D20.2 (A), D21.2 (A), U1.11 (SW0)
/A_SW1: D2.2 (A), D7.2 (A), D10.2 (A), D14.2 (A), D19.2 (A), D22.2 (A), U1.12 (SW1)
/A_SW2: D3.2 (A), D6.2 (A), D11.2 (A), D15.2 (A), D18.2 (A), D23.2 (A), U1.13 (SW2)
/A_SW3: D4.2 (A), D5.2 (A), D12.2 (A), D16.2 (A), D17.2 (A), D24.2 (A), U1.14 (SW3)
/A_VCAP: C5.1, U1.25 (VCAP)
/E0_A: ENC1.A, RN1.1 (R1.1), U2.6 (D7)
/E0_B: ENC1.B, RN1.2 (R2.1), U2.5 (D6)
/E0_SW: ENC1.S1, RN1.3 (R3.1), U2.4 (D5)
/E1_A: ENC2.A, RN1.4 (R4.1), U2.3 (D4)
/E1_B: ENC2.B, RN2.1 (R1.1), U2.14 (D3)
/E1_SW: ENC2.S1, RN2.2 (R2.1), U2.13 (D2)
/SCL: J1.8, R2.1, U1.28 (SCL_SCLK)
/SDA: J1.7, R1.1, U1.29 (SDA_MOSI)
/SR_CLK: J1.12, U2.2 (CP)
/SR_IN: J1.14, R3.1, U2.10 (DS)
/SR_OUT: J1.13, U2.9 (Q7)
/~INT: J1.9
/~SR_LOAD: J1.11, U2.1 (~PL)
GND: C1.2, C2.2, C3.2, C4.2, C5.2, C6.2, C7.2, ENC1.C, ENC1.MP, ENC1.S2, ENC2.C, ENC2.MP, ENC2.S2, J1.3, J1.4, J1.6, J1.10, U1.26 (IFS), U1.27 (VSYNC), U1.30 (ADDR0_MISO), U1.31 (ADDR1_SS), U1.33 (GND), U2.8 (GND), U2.15 (~CE)

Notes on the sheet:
Module bus (R123): J1 to P1 (I2C channel 1 of P1's TCA9546A); chain: P1 buttons -> M3 -> W1
Encoders Tempo, Swing (EC11E, frame MP on GND: no touch, P102) -> 74HC165
LED rings: one LP5864 (24 RGB = 4 SW x 18 CS), 12 LEDs per ring

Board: 2 copper layers, 46 parts (15 on the bottom side), 38 nets, no tracks yet.
